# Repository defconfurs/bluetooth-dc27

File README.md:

# bluetooth-dc27
Bluetooth Firmware for the DC27 DEFCON Furs badge

On my Ubuntu 16.04 development machine, I needed to install the following
prerequisites to build the BLE firmware:
 * pip3 install --upgrade cmake
 * apt-get install ninja
 * apt-get install gperf
 * sudo ln -s /usr/bin/ninja /usr/sbin/ninja
 * export GNUARMEMB_TOOLCHAIN_PATH=/usr
 * export ZEPHYR_TOOLCHAIN_VARIANT=gnuarmemb
 * Download and install device-tree-compiler package from Ubuntu cosmic.

Build the badge BLE firmware:
 * export GNUARMEMB_TOOLCHAIN_PATH=/usr
 * ZEPHYR_TOOLCHAIN_VARIANT=gnuarmemb
 * cd into your zephyr source checkout
 * apply add-i2c-slave-hal.patch to your zephyr sources.
 * source zephyr-env.sh
 * cd into the BLE firmware checkout
 * mkdir build && cd build
 * cmake -GNinja ..
 * ninja

This code is not exactly my finest work, it was the product of a last minute
hackathon, as per usual with all DEFCON projects. My appologies for any
bugs or missing documentation.

Bluetooth Beacon Format
-----------------------
The Bluetooth beacon format follows the #badgelife BLE communcation spec,
which establishes a GAP beacon format that is approximately standardized
between badge makers. Badges are required to set an appearance code of
0x27DC and include a complete badge name.

| Mfr ID | Magic Byte | Byte 0    | Byte 1    | Bytes 3   | Description
|--------| -----------|-----------|-----------|-----------|-----------
| 0x71ff | 0x00       | Badge ID  | Badge ID  |           | Normal Operation
| 0x71ff | 0xa0       | Origin ID | Origin ID |           | Awoo Beacon
| 0x71ff | 0xb2       | Color Hue | ASCII     | ASCII     | Emote Beacon
| 0x71ff | 0xc3       | Color Hue | Time msec | Time msec | Color suggestion beacon.

The badge ID is calculated as an 16-bit CCITT CRC of the bluetooth module's
hardware device ID.

The color hue is in units of 3 degrees (eg: 0=red, 40=green, 80=blue, 120=red
and etc), with the values 0x7e reserved for white, and 0x7f to let the badge
select a random color.

The color suggestion beacon was planned for coordinated lighting effects from
the DJ console, but was never implemented in the badge and animation codebase
because we ran out of time.

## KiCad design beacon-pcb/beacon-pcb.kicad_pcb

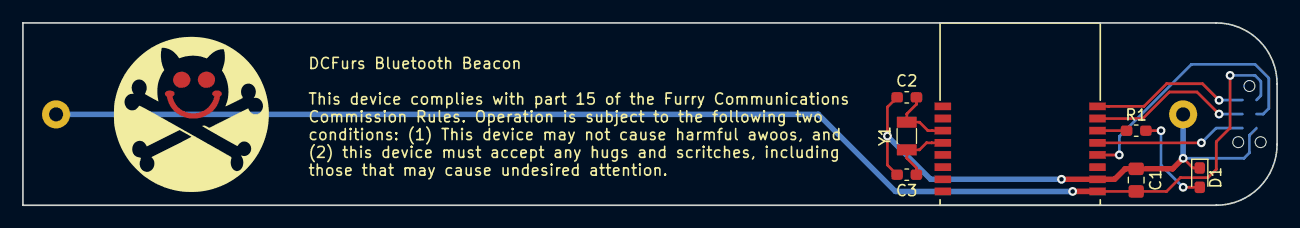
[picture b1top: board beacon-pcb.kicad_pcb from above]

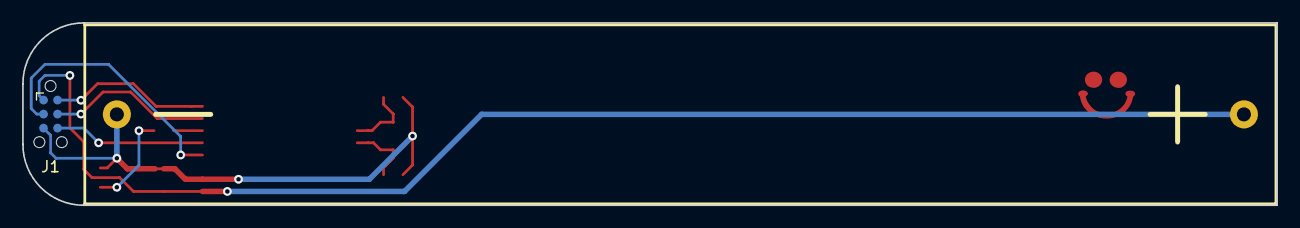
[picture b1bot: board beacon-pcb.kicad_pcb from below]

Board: 2 copper layers, 113.5 x 16.5 mm, 10 parts (2 on the bottom side), 10 nets.

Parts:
BT1: Battery; BAT-2xAA-BC12AAPC
C1: 4.7u; C_0805_2012Metric_Pad1.15x1.40mm_HandSolder
C2, C3: 15p; C_0603_1608Metric_Pad1.05x0.95mm_HandSolder
D1: LED_ALT; LED_0603_1608Metric_Pad1.05x0.95mm_HandSolder
IC1: BT832
J1: TC2030-CTX-NL; Tag-Connect_TC2030-IDC-NL_2x03_P1.27mm_Vertical
R1: 100; R_0603_1608Metric_Pad1.05x0.95mm_HandSolder
Y1: 32.768kHz; Crystal_SMD_3215-2Pin_3.2x1.5mm
dcfurs-logo: dcfurs-logo

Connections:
+BATT: BT1.1, C1.1, IC1.9, J1.1
/SWCLK: IC1.15, J1.4
/SWDIO: IC1.16, J1.2
/UART_RXD: IC1.13, J1.6
/UART_TXD: IC1.12, J1.3
GND: BT1.2, C1.2, C2.2, C3.2, D1.1, IC1.10, J1.5
unnamed: C2.1, IC1.3, Y1.1
unnamed: C3.1, IC1.4, Y1.2
unnamed: D1.2, R1.2
unnamed: IC1.14, R1.1

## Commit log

2019-07-06 Add Zephyr board support for the BT832A module.
2019-07-08 Add quick PCB project for BLE beacon.
2019-07-08 Add DC26 BLE firmware sources.
2019-07-08 Fix build error: crc16.h not found.
    Over the last year, the Zepyr project unified their CRC headers and
    moved it all to sys/crc.h instead.
2019-07-20 Release beacon PCB for manufacture.
2019-07-20 Update beacon IDs for DEFCON 27.
2019-07-21 Add I2C slave interface to the BLE module.
    We hope to make more of the BLE status and config things available
    through I2C, which will make the BLE module behave more like a
    peripheral.
2019-07-21 Move beacon handling to separate file, add color suggestion.
2019-07-22 Add registers to initiate a beacon transmission.
    Writing to the TXLEN register will cause the badge to initiate a beacon
    transmission for 1s using the contents of the TXMAGIC and TXDATA registers.
    The beacon will be sent at the fast advertising rate for 1s after which
    the badge will return to the normal beacon at the slow rate.
    There is some concern over the maximum beacon payload, so we have also
    reduced the size of the badge name string to guarantee space for a few
2019-07-25 Reorganize project into badge and beacon firmware.
2019-07-28 Remove serial number from #badgelife header.
    To make room for more payload, we removed the serial number from the
    DCFurs/#badgelife beacon header to make room for the new color suggestion
    field. The serial number is still included in normal advertising beacon
    though.
2019-08-05 Fix TTL propagation in the Awoo beacons.
2019-08-05 Change beacon color to use hue from 0-120 degrees.
    This gives 7-bits of color selection in beacons using HSV
    color space, with a couple extra reserve values for things
    like white (0x7e) and random (0x7f).
2019-08-05 Add FCC/I2C text blob as an easter egg.
2019-08-05 Use a periodic timer to clear magic beacon effects.
    It has rarely been observed where badges will fail to clear an emote
    or awoo status, I suspect that this is being caused by a race between
    the beacon refresh worker and the reception of a new beacon. As an
    attempt to make the badge more reliable, we move the expiration
    timing into a periodic timer so that it gets caught on the next
    iteration.
2019-08-05 Deadlock fix: The threadening
    Replacing one-shot timers with periodic timers doesn't seem to have
    fixed the deadlock condition, so lets try it again using threads,
    which hopefully give us better scheduling control.
2019-08-06 Deadlock fix: Release the watchhounds!
    Splitting the expiration timing into a thread did not entirely solve
    the crash. So lets enable the hardware watchdog to reboot the SoC if
    all else fails.
2019-08-06 Add badge flasher script.
2019-08-07 Reduce I2C buffer size for nrf52832 builds.
    The nrf52832 has a smaller buffer size than the nrf52810, which was causing
    I2C read/write access to hang due to setting and invalid size.
2019-08-14 Extremely sloppy pass at documentation cleanup.
2019-09-09 typo for magic numbers
